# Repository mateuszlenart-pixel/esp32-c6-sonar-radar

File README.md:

# Radar sonarowy ESP32-C6

Firmware dla płytki ESP32-C6-DevKitC-1. Radar obraca serwo, wykonuje pomiary odległości sonarem i pokazuje stan na ekranie OLED oraz matrycy LED. Buzzer sygnalizuje stan krytyczny. Opcjonalna obsługa Wi-Fi działa w trybie stacji.

## Wymagania

- Linux z PlatformIO Core
- ESP32-C6-DevKitC-1 do późniejszego testu sprzętowego
- Płytka nie jest potrzebna do kompilacji ani testów hostowych

## Kompilacja firmware'u

W katalogu repozytorium uruchom:

```bash
$HOME/.platformio/penv/bin/pio run
```

PlatformIO używa środowiska `esp32-c6-devkitc-1` z `platformio.ini`. Kompilacja tworzy pliki w katalogu `.pio/`.

## Testy hostowe

Testy nie wymagają ESP32 ani podłączonych czujników. Uruchom je w katalogu repozytorium:

```bash
gcc -std=c11 -Wall -Wextra -Werror -Isrc src/detector.c tests/test_detector.c -o /tmp/test_detector && /tmp/test_detector
```

```bash
gcc -std=c11 -Wall -Wextra -Werror -Isrc src/scan_control.c tests/test_scan_control.c -o /tmp/test_scan_control && /tmp/test_scan_control
```

```bash
gcc -std=c11 -Wall -Wextra -Werror -Isrc src/usb_cc.c tests/test_usb_cc.c -o /tmp/test_usb_cc && /tmp/test_usb_cc
```

GitHub Actions uruchamia wszystkie trzy zestawy testów oraz kompiluje firmware przy pushu na `main` i przy pull requestach.

## Buzzer

Płytka ma tranzystorowy stopień (Q2) i diodę (D2), więc pasuje zarówno buzzer pasywny, jak i aktywny
na 5 V. W `src/app_config.h` ustaw `BUZZER_ACTIVE`:

- `0` (domyślnie): buzzer pasywny, firmware generuje ton PWM i alarm krytyczny ma wyraźnie inne tony;
- `1`: buzzer aktywny, firmware tylko włącza i wyłącza, a różnice zostają w rytmie sygnału.

## Wi-Fi

Bez lokalnego pliku z danymi Wi-Fi firmware pomija uruchomienie Wi-Fi, a lokalne funkcje radaru nadal działają.

Aby skonfigurować Wi-Fi na swoim komputerze:

1. Skopiuj `src/wifi_credentials.example.h` do `src/wifi_credentials.h`.
2. Wypełnij lokalnie nazwę sieci 2,4 GHz i jej hasło.
3. Skompiluj firmware ponownie.

Plik `src/wifi_credentials.h` jest ignorowany przez Git. Nie umieszczaj danych sieciowych w repozytorium, logach ani wiadomościach.

## Jak działa firmware

- `radar.c` steruje ruchem patrolowym serwa. Patrol obejmuje kąty od 15° do 165° i zatrzymuje się podczas blokady na wykrytym celu.
- `sonar.c` wykonuje pojedynczy pomiar, a `sonar_task.c` przekazuje wyniki dalej.
- `detector.c` wykrywa cel i alarm krytyczny na podstawie kolejnych pomiarów.
- `ui_task.c`, `oled.c`, `matrix.c` i `buzzer.c` obsługują ekran, matrycę i sygnał dźwiękowy.
- `power_monitor.c` mierzy przez ADC napięcie szyny 5 V (GPIO0) oraz linie CC1/CC2 gniazda USB-C zasilania
  (GPIO1, GPIO3) i czyta flagę przeciążenia przełącznika U2 (GPIO23). Co 30 s oraz przy każdej zmianie
  zapisuje wynik w logu i ostrzega, gdy zasilacz podaje tylko 500/900 mA, szyna 5 V spadnie poniżej 4,5 V
  albo U2 ogranicza prąd. Klasyfikacja CC jest w `usb_cc.c` (testy hostowe). Działa na płytce PCB;
  na breadboardzie bez tych elementów odczyty są przypadkowe, a log tylko informacyjny.
- `network.c` obsługuje połączenie Wi-Fi oraz ponawianie połączenia.
- `zigbee_bridge.c` udostępnia czujniki i przełączniki przez Zigbee.
- `mqtt_bridge.c` publikuje stan radaru oraz każdy kolejny pomiar po MQTT.

## Home Assistant, Zigbee2MQTT i MQTT

ESP32-C6 działa jako urządzenie Zigbee typu End Device. Połączenie Wi-Fi i Zigbee
korzysta z tej samej anteny 2,4 GHz, więc End Device ogranicza ryzyko problemów
ze współpracą obu sieci. Koordynator SONOFF Dongle-PMG24 pozostaje podłączony do
Zigbee2MQTT; nie trzeba zmieniać jego firmware.

### Encje Zigbee

Plik `zigbee2mqtt/radar_converter.mjs` opisuje encje dla Zigbee2MQTT. Umieść go
w folderze `external_converters` obok `configuration.yaml` w katalogu danych
Zigbee2MQTT. W dodatku Home Assistanta domyślny katalog danych to
`/config/zigbee2mqtt`, więc pełna ścieżka pliku to
`/config/zigbee2mqtt/external_converters/radar_converter.mjs`.

W Zigbee2MQTT 2.11 lub nowszym włącz `advanced.enable_external_js`. Konwerter
można też dodać lub zmienić w interfejsie Zigbee2MQTT w **Settings → Dev console
→ External converters**. Po dodaniu pliku uruchom ponownie Zigbee2MQTT. Następnie
włącz dozwolone dołączanie urządzeń i uruchom radar. Po wykryciu radaru zaakceptuj
nowe urządzenie.

Zigbee udostępnia wykrycie celu, alarm krytyczny, odległość, kąt, dwa progi
odległości oraz przełączniki patrolu i buzzera. Próg celu można ustawić w zakresie
10–400 cm, a krytyczny w zakresie 5–300 cm. Próg krytyczny musi być mniejszy od
progu celu. Po dołączeniu Z2M konfiguruje raportowanie zmian.

### MQTT i Home Assistant

Skopiuj `src/wifi_credentials.example.h` do lokalnego pliku
`src/wifi_credentials.h`. W tym lokalnym pliku wpisz dane Wi-Fi i adres brokera
MQTT; jeśli broker wymaga logowania, wpisz je tam. Nie wysyłaj tych wartości na
czat i nie dodawaj lokalnego pliku do Git. MQTT Discovery automatycznie tworzy
encje w Home Assistant. Topic `esp32-c6-sonar-radar/<identyfikator>/state`
zawiera aktualny stan, a topic `.../scan` przekazuje kolejne pomiary z kątem,
odległością i informacją, czy pomiar był prawidłowy.

W tej wersji testowano kompilację i logikę programową. Dołączenie urządzenia,
raportowanie Zigbee, encje Home Assistant i fizyczne pomiary wymagają późniejszego
testu z płytką oraz działającym Zigbee2MQTT i brokerem MQTT.

## Test sprzętowy

Szczegółowy plan testów i szkic połączeń znajduje się w
[`docs/hardware/radar-wiring-and-test-plan.md`](docs/hardware/radar-wiring-and-test-plan.md).
Interaktywny model breadboardu (sieci, kontrola zwarć, edycja położenia elementów)
uruchomisz, otwierając w przeglądarce plik
[`docs/hardware/breadboard-model.html`](docs/hardware/breadboard-model.html).

Kompilacja i testy hostowe nie sprawdzają płytki, serwa ani czujników. Przed pierwszym testem sprzętowym należy osobno zweryfikować zasilanie, poziomy napięć i połączenia dla dokładnych modeli modułów. Plik `src/app_config.h` zawiera przypisania GPIO, ale sam w sobie nie jest schematem bezpiecznego okablowania.

### Poziomy napięć do sprawdzenia

- ESP32-C6 pracuje z GPIO w domenie 3,3 V. Jego wejście nie może przekroczyć 3,6 V ([datasheet Espressif, tabele 5-1 i 5-4](https://documentation.espressif.com/esp32-c6_datasheet_en.html)). Nie podłączaj bezpośrednio wyjścia ECHO typowego modułu HC-SR04 zasilanego z 5 V; obniż poziom sygnału przed GPIO. Dokładne wersje HC-SR04 mogą się różnić ([przykładowa dokumentacja modułu Elecfreaks](https://elecfreaks.com/download/EF03085-HC-SR04_Ultrasonic_Module_User_Guide.pdf)).
- Jeśli sam układ MAX7219 jest zasilany napięciem 5 V, jego datasheet wymaga co najmniej 3,5 V na wejściu logicznym. ESP32-C6 gwarantuje dla wyjścia logicznego wysokiego co najmniej 0,8 × 3,3 V = 2,64 V, więc bezpośrednia współpraca nie jest gwarantowana. Trzeba sprawdzić, czy konkretny moduł ma właściwy translator poziomów ([datasheet Analog Devices MAX7219, tabela na stronie 2](https://www.analog.com/media/en/technical-documentation/data-sheets/max7219-max7221.pdf)).

Te uwagi nie zastępują sprawdzenia oznaczeń i schematów dokładnych modułów. Nie podłączaj serwa do zasilania, dopóki jego napięcie i wydajność prądowa nie zostaną potwierdzone dla użytej płytki zasilającej.

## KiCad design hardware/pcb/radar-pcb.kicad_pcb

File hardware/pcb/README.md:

# Płytka PCB radaru (KiCad 10)

> **Stan 2026-10-15: wersja przewlekana v0.2** (76 × 137,5 mm, wszystko lutowane ręcznie, gniazdo DC zamiast USB-C,
> piny DevKita wyprowadzone na listwy, pole prototypowe). Opisy poniżej (USB-C, U2, SMD, rozmieszczenie ręczne)
> dotyczą wcześniejszej wersji SMD v0.1 i są **historyczne**; aktualne decyzje: [`order-notes.md`](order-notes.md).
> Generatory: `tools/gen_schematic.py` (schemat), `tools/autoplace.py` (rozmieszczenie, `tools/geom.py` = kotwice i strefy),
> `tools/gen_pcb.py` (płytka), `tools/build_all.sh` (całość, `SKIP_PLACE=1` używa zapisanego `tools/layout.json`).

Status: **start projektu 2026-10-10.** Zamówienie dopiero po sprawdzeniu na breadboardzie
wszystkich bloków i po kontrakcie mechanicznym (zob. `../README.md`).

## Narzędzia (Dell, Flatpak `org.kicad.KiCad` 10.0.7)

- Biblioteki symboli i footprintów: `/app/extensions/Library/{symbols,footprints,3dmodels}`
  wewnątrz Flatpaka (`flatpak run --command=sh org.kicad.KiCad -c '...'`).
- Python z modułem `pcbnew` (10.0.7) w tym samym Flatpaku: skrypty tworzą i sprawdzają płytkę.
- `kicad-cli`: ERC, DRC, eksport Gerberów, BOM, podgląd 3D.
- Brak Javy, więc bez Freerouting; trasowanie ręczne/skryptem (płytka jest prosta).

## Bloki obwodu (z breadboardu, stan na 2026-10-10)

| Blok | Stan na breadboardzie |
|---|---|
| Zasilanie 5 V z EB2005 | zmierzone (5,13 V) |
| HC-SR04: TRIG przez SN74AHCT125, ECHO przez dzielnik 10 kΩ/15 kΩ | działa, ±1 cm |
| OLED SH1106, I2C, 3,3 V z ESP32 | działa |
| MAX7219 przez kanały 2–4 AHCT125 | zaparkowane, plan gotowy |
| Serwo SG90, 5 V | nie podłączone |
| Buzzer (tranzystor) | nie podłączone, typ nieustalony |

## Domyślne założenia projektowe (DO ZATWIERDZENIA przez użytkownika)

1. **ESP32-C6-DevKitC-1 w gniazdach żeńskich** (decyzja użytkownika z 2026-10-09).
   Rozstaw rzędów do potwierdzenia na posiadanej płytce przed layoutem.
2. **Zasilanie wejściowe (zmiana 2026-10-11):** gniazdo **USB-C tylko do zasilania** (HRO TYPE-C-31-M-12, od 2026-10-14; wcześniej GCT USB4105,
   montaż maszynowy) zamiast gniazda DC. Rezystory 5,1 kΩ na CC1/CC2 (R16, R17) są konieczne, żeby
   ładowarka z kablem USB-C ↔ USB-C podała 5 V. Ochrona: TVS 5 V (D3, SMAJ5.0A, jednokierunkowy) na wejściu oraz przełącznik obciążenia z miękkim startem
   i ogranicznikiem prądu U2 (**AP22802AW5-7**, LCSC C211404, od 2026-10-14; zastąpił AP22804AW5, którego nie ma w katalogu JLCPCB; ten sam układ wyprowadzeń SOT-25, EN aktywny wysokim, EN połączone z VIN, RDS(on) typ. 50 mΩ, limit prądu 2,2–3,2 A, typ. 2,7 A, znamionowo 2 A) zamiast
   bezpiecznika polimerowego (mniejszy spadek napięcia, miękki start i ograniczenie prądu przy ładowaniu ok. 900 µF; patrz uwagi do weryfikacji niżej); zabezpieczenie przed odwrotną polaryzacją (Q1) usunięte, bo USB-C nie da się
   podłączyć odwrotnie. Linie danych USB (D+/D−, SBU) niepodłączone. Wejście 5 V zasila serwo, HC-SR04,
   MAX7219, bufor i ESP32. Wymagana ładowarka ≥ 5 V / 1,5 A (szczyt poboru około 1–1,3 A); port USB
   komputera (500 mA) może nie wystarczyć.
3. **Pin 5V DevKita (J2 pin 14) jest zasilany z +5V płytki przez diodę Schottky D4** (kierunek płytka →
   DevKit). Poprawka po audycie 2026-10-11: DevKit ma własną diodę 1N5819 od swojego USB do pinu 5V,
   więc bezpośrednie połączenie z +5V pozwalałoby, żeby port USB komputera zasilał całą płytkę (serwo,
   matryca, sonar) i zasilał VBUS gniazda USB-C. Z diodą D4 USB DevKita zasila tylko DevKit
   (programowanie), a przy zasilaniu z USB-C płytki DevKit dostaje około 4,7 V przez D4.
4. **Moduły na złączach 2,54 mm** (gniazda żeńskie na PCB): OLED 1×4, MAX7219 1×5,
   HC-SR04 1×4, serwo 1×3. HC-SR04 i serwo na kablach, bo siedzą na obracanej głowicy.
5. **Bufor SN74AHCT125D w SMD (SOIC-14)** (decyzja po audycie 2026-10-11, montaż maszynowy), wszystkie 4
   kanały użyte (TRIG, DIN, CLK, CS), rezystory 47 kΩ na wejściach A: pull-down na TRIG, DIN i CLK,
   **pull-up do 3,3 V na CS** (w firmware CS spoczynkowo wysoki; na płytce testowej działało z pull-downem),
   100 nF przy VCC.
6. **Dzielnik ECHO 10 kΩ/15 kΩ** na płytce, zgodnie z prototypem.
7. **Buzzer:** tranzystor NPN lub MOSFET z rezystorem bazy i diodą (dla cewki), złącze
   2-pinowe na zewnętrzny buzzer. Typ buzzera do identyfikacji.
8. **Kondensatory odsprzęgające i bulk** na szynie 5 V (np. 470 µF przy serwie i MAX7219).
9. **Punkty testowe** na 5 V, 3V3, GND, TRIG, ECHO (węzeł GPIO6).
10. **Wyłącznik ON/standby:** przycisk chwilowy (tact) na GPIO2 do GND (wewnętrzny pull-up ESP32, opcjonalnie kondensator 100 nF do GND), do tego 2-pinowe złącze na zewnętrzny przycisk w obudowie. To „miękki” wyłącznik: ESP32 zostaje włączone (inaczej nie zadziała Zigbee), a serwo, pomiary, ekrany i buzzer są wyłączone. Opcjonalnie dodatkowo twardy przełącznik w linii 5 V (do decyzji).
11. **Obrys i otwory montażowe:** dopiero z kontraktu mechanicznego (kolumna obudowy
    70 × 50 mm, wnętrze mniejsze o ścianki).

## Stan prac (2026-10-10)

- **Schemat:** `radar-pcb.kicad_sch` (A3), generowany skryptem `tools/gen_schematic.py`
  (połączenia przez etykiety globalne, każdy pin ma sieć albo znacznik NC). 36 elementów,
  41 sieci. ERC (`kicad-cli sch erc`): **0 błędów**, 6 ostrzeżeń `lib_symbol_mismatch`
  dla U1 (osadzona kopia 74AHCT125 jest spłaszczona, bez wpływu na połączenia).
- **Pinout DevKita:** `devkit-pinout.md` (odczytany ze schematu Espressif; poprawka: GND jest
  też na J3 pin 12 i 15).
- **Płytka (szkic automatyczny, 2026-10-10):** `radar-pcb.kicad_pcb`, 66 × 128 mm, dwie warstwy,
  generowana skryptem `tools/gen_pcb.py` z netlisty schematu. Układ (widok od frontu): u góry
  złącza kabli do głowicy (sonar, serwo, buzzer, przycisk zewnętrzny), pod nimi gniazda OLED i
  MAX7219 (moduły wtykane od frontu), od tyłu poziomo DevKit (USB po lewej), gniazdo USB-C zasilania i przycisk
  ON/STANDBY na lewej krawędzi między rzędami pinów DevKita, bufor AHCT (SOIC) między rzędami DevKita. Trasowanie: Freerouting 2.5.0
  (jar + Temurin JRE 25, pobrane do `~/tools`, sumy kontrolne zweryfikowane), potem wylewki GND.
- **Stan DRC (2026-10-11, po audycie):** `kicad-cli pcb drc --schematic-parity`: **0 naruszeń
  (także silkscreen), 0 niepołączonych, 0 niezgodności ze schematem**. Freerouting: 0 nietrasowanych.
  Rozmieszczenie jest wrażliwe: przesunięcie części przy rzędach DevKita potrafi zepsuć trasowanie
  (ścieżki przechodzą między pinami rzędu J3), więc po każdej zmianie uruchamiać `build_all.sh`.
  Wszystkie elementy mają ręcznie zaplanowane pozycje (`FIXED` w `gen_pcb.py`), pas 0,9 mm przy
  krawędzi jest wolny od ścieżek, wylewki GND na obu warstwach.
- **Opisy na płytce (silkscreen):** przy każdym złączu nazwa modułu i nazwa każdego pinu (sonar,
  serwo, buzzer, przycisk, OLED, MAX7219), od tyłu opis wszystkich 32 pinów DevKita z kierunkiem
  USB-C, przy elementach oznaczenie z wartością (np. „R6 10k”, „C1 470uF 16V”), polaryzacja
  („+” przy elektrolitach, „K” przy katodach diod, „1” przy pinie 1 bufora), opisy punktów
  testowych, gniazda USB-C i przycisku ON/STANDBY. DRC: 0 naruszeń.
- **Przycisk ON/STANDBY:** kątowy (C&K PTS645VL58-2LFS, footprint `SW_Tactile_SPST_Angled_PTS645Vx58-2LFS`)
  na lewej krawędzi; popychacz wystaje ok. 3,3 mm poza płytkę, w osi 65,75 mm od górnej krawędzi
  (otwór w ściance obudowy). Złącze J9 zostaje na ewentualny przycisk panelowy.
- **Rysunek do weryfikacji:** `renders/radar-pcb-v0.1-wymiary-do-weryfikacji.pdf` (A4, strony 1-2
  w skali 1:1: przód i tył z wymiarami W1-W12 oznaczonymi „?”, strona 3: podgląd 3D). Wymiary
  są w skrypcie (`DIMS` w `gen_pcb.py`), legenda na warstwach Dwgs.User (przód) i Cmts.User (tył).
- **Ochrona przed zakłóceniami matrycy (2026-10-11, z testów na breadboardzie):** filtr RC zasilania
  sonaru (R11 10 Ω + C6 100 µF + C7 100 nF, sieć SR04_VCC na J4 pin 1), rezystory szeregowe
  100 Ω na DIN/CLK/CS do MAX7219 (R12–R14, sieci *_J na J6) i kondensatory przy module (C8 100 µF,
  C9 100 nF). Na breadboardzie przełączanie wierszy MAX7219 i transmisja do niej dawały fałszywe
  echa HC-SR04; firmware obchodzi to gaszeniem matrycy na czas pomiaru (widoczne lekkie mruganie).
  Te elementy mają pozwolić z tego obejścia zrezygnować; nie są jeszcze sprawdzone na płytce.
- **Serwo i buzzer (2026-10-11, analiza zakłóceń przed testem):** serwo SG90 pobiera impulsy prądu
  rzędu setek mA i jest zasilane z tej samej szyny 5 V co sonar, bufor i matryca. Dlatego +5V serwa
  idzie przez FB1 (miejsce na ferryt ≥ 1 A albo zworkę 0 Ω) do sieci SERVO_5V, z C4 220 µF i C10 100 nF
  przy złączu J5 (C4 przeniesiony z lewego pasa pod J5). R15 10 kΩ ciągnie sygnał serwa do masy,
  gdy GPIO10 jest nieustawione (reset, start). Buzzer: C11 100 nF na +5V przy sterowniku Q2/J8
  (przełączanie 2 kHz), dioda D2 już była; C12 100 nF równolegle do buzzera jest miejscem
  opcjonalnym. Nie sprawdzone na sprzęcie.
- **Zmiany po audycie (2026-10-11), wszystkie wdrożone:** D4 (punkt 3 wyżej); pod anteną DevKita
  (x ≥ 57, y 91–121) strefa bez miedzi na obu warstwach, punkty TP1/TP3 przeniesione; TVS jednokierunkowy;
  przełącznik obciążenia U2 zamiast F1 (spadek napięcia, miękki start; pełne odcięcie w STANDBY nie jest
  zrobione, bo ESP32 zasila się z tej samej szyny); FB1 domyślnie zworka 0 Ω; punkt testowy SERVO_5V
  (TP6); przycisk zewnętrzny: R18 1 kΩ szeregowo i R19 10 kΩ pull-up po stronie kabla (J9); pomiar
  napięcia 5 V dla firmware (R20/R21 → IO0, C13); złącze awaryjne J10 (RST, GND, BOOT = IO9: zwarcie
  sąsiednich pinów); miejsca R24/R25 4,7 kΩ na pull-upy I2C (nie montować); CS z pull-upem; bufor SOIC.
  Firmware jeszcze nie czyta ADC. Ścieżka VIN ma 0,5 mm (szersza nie mieści się przy padach USB-C 0,5 mm).
  Pomiary CC1 i CC2 przez ADC (R22/R23 100 kΩ, C14/C15 100 nF → IO1 i IO3) są wdrożone; elementy stoją
  tuż przy pinach 8 i 13 DevKita między rzędami (wcześniejsze ustawienie przy złączu USB-C nie dawało
  się poprowadzić).
- **Układ lewej krawędzi (2026-10-13, decyzja użytkownika):** oba gniazda USB-C (zasilania na froncie, programowania
  DevKita od tyłu) są po lewej stronie; gniazdo zasilania ma oś 100 mm od górnej krawędzi (W6), przycisk
  ON/STANDBY 113 mm (W7), oba między rzędami pinów DevKita (94–117 mm), czyli nisko na płytce. Na prawej
  krawędzi, w strefie anteny DevKita, nie ma już metalu ani miedzi. Przeniesiono za gniazdem: R16/R17 (CC),
  D3 (TVS), U2, C16, LED zasilania (D1/R1, wyżej po lewej), R18/R19/C5 (przycisk), punkty TP2/TP4 i dzielnik
  R20/R21/C13 (na dole). Na obudowie opisać, które gniazdo jest zasilające, a które do programowania.
  **W6 (100 mm), W7 (113 mm), W8 (59 mm) i W9 (92 mm) zatwierdzone przez użytkownika 2026-10-13**; wszystkie wymiary
  W1–W12 w PDF mają teraz „OK”. DRC i trasowanie przechodzą (0 naruszeń).
  Generator usuwa ślepe przelotki po imporcie wyniku Freeroutingu (Freerouting zgłasza 3 nietrasowane
  połączenia, a KiCad po imporcie ma 0 niepołączonych; sprawdzone przez DRC).
- **DevKit (zmierzone 2026-10-13):** laminat 52,0 × 25,4 mm, z anteną 58,5 × 25,4 mm; od pinu 1 do końca
  płytki od strony anteny oraz od pinu 16 do końca od strony USB po ok. 7 mm (zgadza się z (52,0 − 38,1)/2 ≈ 6,95).
  Przy pinie 1 na x = 55 mm laminat sięga x ≈ 62, a antena modułu ok. 68,5 mm, czyli ok. 2,5 mm poza prawą
  krawędź płytki. Strefa bez miedzi (x ≥ 57, y 91–121) obejmuje antenę z zapasem, więc **nie zmienia się**.
  Koniec USB DevKita leży przy x ≈ 10 mm, ok. 10 mm od lewej krawędzi płytki.
- **Moduły (zmierzone 2026-10-13):** OLED SH1106 33,5 × 35,5 mm, piny 13,5 mm od krawędzi do osi pierwszego i
  ostatniego, kolejność VCC, GND, SCK, SDA od strony wyświetlacza; MAX7219 32 × 39 mm, piny 11 mm od krawędzi,
  piny wystają poza obrys na wymiarze 39 mm po ok. 6 mm na stronę; HC-SR04 VCC/TRIG/ECHO/GND i serwo SG90
  3-pin 2,54 mm potwierdzone. Gniazda J7 (OLED) i J6 (MAX7219) są wyśrodkowane na x = 33 mm, co zgadza się z pomiarami.
- **Drugi audyt (2026-10-11), wdrożone:** U2 i C16 stoją tuż przy gnieździe USB-C (VIN jest krótki,
  dalej idzie `+5V` ścieżką 0,6–0,8 mm; wcześniej VIN miał ok. 41 mm i spadek napięcia nie malał); LED
  zasilania (D1, R1) przeniesiona niżej; złącze J10 stoi między rzędami DevKita blisko pinów RST (J1 pin 2)
  i GPIO9 (J3 pin 11), więc linie EN i BOOT są krótkie (wcześniej 63 i 21 mm); FLG z U2 prowadzi do GPIO23
  (J3 pin 5, pull-up R26 10 kΩ do 3,3 V; niski = przeciążenie), firmware do dopisania.
  **J10:** kolejność BOOT, GND, RST. Wgrywanie awaryjne: zworka na BOOT–GND, odłączyć i podłączyć
  zasilanie, wgrać firmware, zdjąć zworkę i zrobić reset (zworka na GND–RST na chwilę). Jedna zworka
  obejmuje tylko jedną parę pinów naraz.
  **Otwór H4** (62,5; 124) leży ok. 8 mm od anteny; zalecane nylonowe śruby i tuleje (metal przy
  antenie obniża zasięg). Położenie otworów jest częścią kontraktu mechanicznego i nie zostało zmienione.
  **Uwagi dla firmware:** odczyt CC1/CC2 (GPIO1, GPIO3) dopiero po kilku sekundach od podłączenia
  (ładowarki PD wysyłają komunikaty po CC), mediana z kilku próbek, wewnętrzne pull-upy na tych pinach
  wyłączone. GPIO0 i GPIO1 to też piny kwarcu 32 kHz; na schemacie DevKitC-1 v1.4 kwarcu nie ma
  (sprawdzone wyszukiwaniem w tekście schematu), więc nie koliduje.
  **Przepięcie (świadomie bez zmiany):** TVS SMAJ5.0A ogranicza impulsy, ale przy trwałym nadnapięciu
  z wadliwej ładowarki (np. 9 V) spali się, a AP22802 nie ma ochrony nadnapięciowej. Zgodna ładowarka
  przy rezystorach 5,1 kΩ na CC nie poda więcej niż 5 V, więc ryzyko jest szczątkowe. Zamiana na eFuse
  z OVP (rodzina TI TPS2595x) wymaga potwierdzenia dostępności, footprintu i karty katalogowej, a
  symbolu nie ma w bibliotece KiCada. Opcja na kolejną rewizję.
  **Do sprawdzenia przed zamówieniem:** wariant AP22802**A**W5-7 (EN aktywny wysokim; potwierdzone
  w karcie katalogowej Diodes: pin 4 EN, A = aktywny wysokim, B = niskim); dopuszczalna pojemność wyjściowa i
  zachowanie przy przegrzaniu (za U2 jest ok. 900 µF, start trwa kilka ms w limicie prądu 2,2–3,2 A; AP22802 startuje wolniej niż AP22804, rise time typ. 2,1 ms przy 4,7 µF);
  start z pełną pojemnością i ładowarką 1,5 A na prototypie. Limit prądu U2 jest wyższy niż 1,5 A
  ładowarek USB-C: chroni przed zwarciem, ale ładowarka ma własne zabezpieczenie.
- **Rendery i PDF:** `tools/export_docs.sh` (po `build_all.sh`).
- **Do sprawdzenia przed zamówieniem:** gniazdo USB-C HRO TYPE-C-31-M-12 (footprint z biblioteki KiCad; zmienione z GCT USB4105-xx-A 2026-10-14) – potwierdzić
  dostępność u wykonawcy montażu; dopuszczalny odstęp 0,19 mm pól GND od otworów pozycjonujących jest
  z zaleceń producenta (ustawione w `.kicad_pro`); położenie gniazd modułów po pomiarach (rozstaw rzędów DevKita zmierzony: 23,1 mm).
- **Obrys 66 × 128 mm i położenie elementów to propozycja** do zatwierdzenia po zmierzeniu
  modułów i DevKita. **Zmierzone 2026-10-13 (suwmiarka 0,05 mm):** rozstaw rzędów DevKita 23,1 mm (W10;
  wcześniej zakładane 23,3), długość listwy 38,1 mm (W11), pin 1 11,0 mm od prawej krawędzi (W12), odstęp
  gniazd OLED–MAX7219 42,0 mm (W5). Otwory M3: H1–H4 tworzą prostokąt 59 × 92 mm, x = 3,5 i 62,5, y = 32 i 124.
- **Odtworzenie całości jednym poleceniem** (z katalogu repo): `hardware/pcb/tools/build_all.sh`
  (schemat, ERC, netlista, rozmieszczenie, Freerouting, wylewki GND, DRC; ok. 1,5 min).
- **Następne:** poprawić rozmieszczenie i trasowanie do DRC bez błędów, przegląd użytkownika w
  KiCadzie, kontrakt mechaniczny.

## Plan pracy

1. Zatwierdzenie założeń powyżej.
2. Kontrakt mechaniczny: ułożenie płytki w kolumnie 70 × 50 × 155 mm.
3. Schemat KiCad (skrypt generujący `.kicad_sch`, ERC bez błędów).
4. Netlista i płytka (`pcbnew` w Pythonie), rozmieszczenie, trasowanie, DRC.
5. Przegląd użytkownika w KiCadzie (podgląd 3D), poprawki.
6. Gerbery, BOM, CPL do JLCPCB lub PCBWay, zamówienie po teście prototypu.

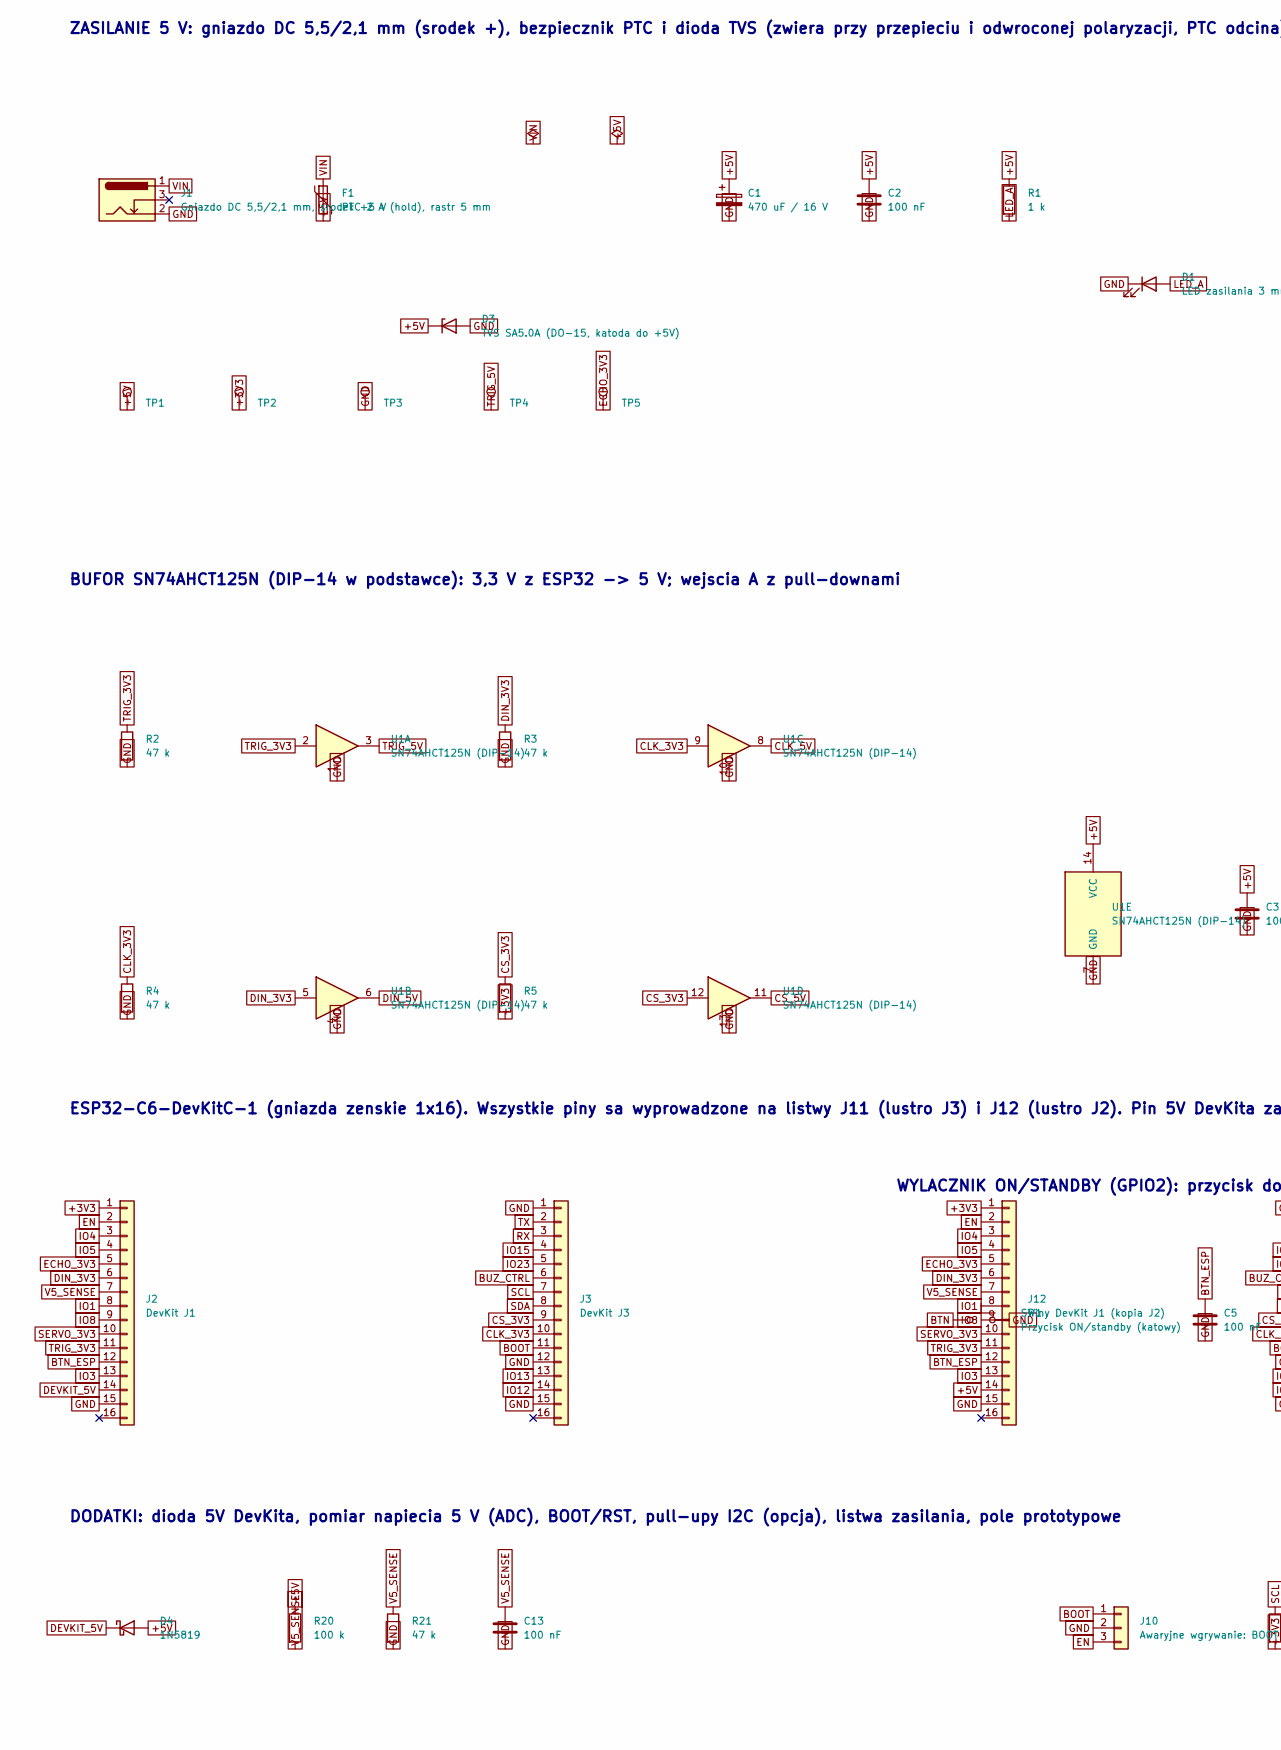
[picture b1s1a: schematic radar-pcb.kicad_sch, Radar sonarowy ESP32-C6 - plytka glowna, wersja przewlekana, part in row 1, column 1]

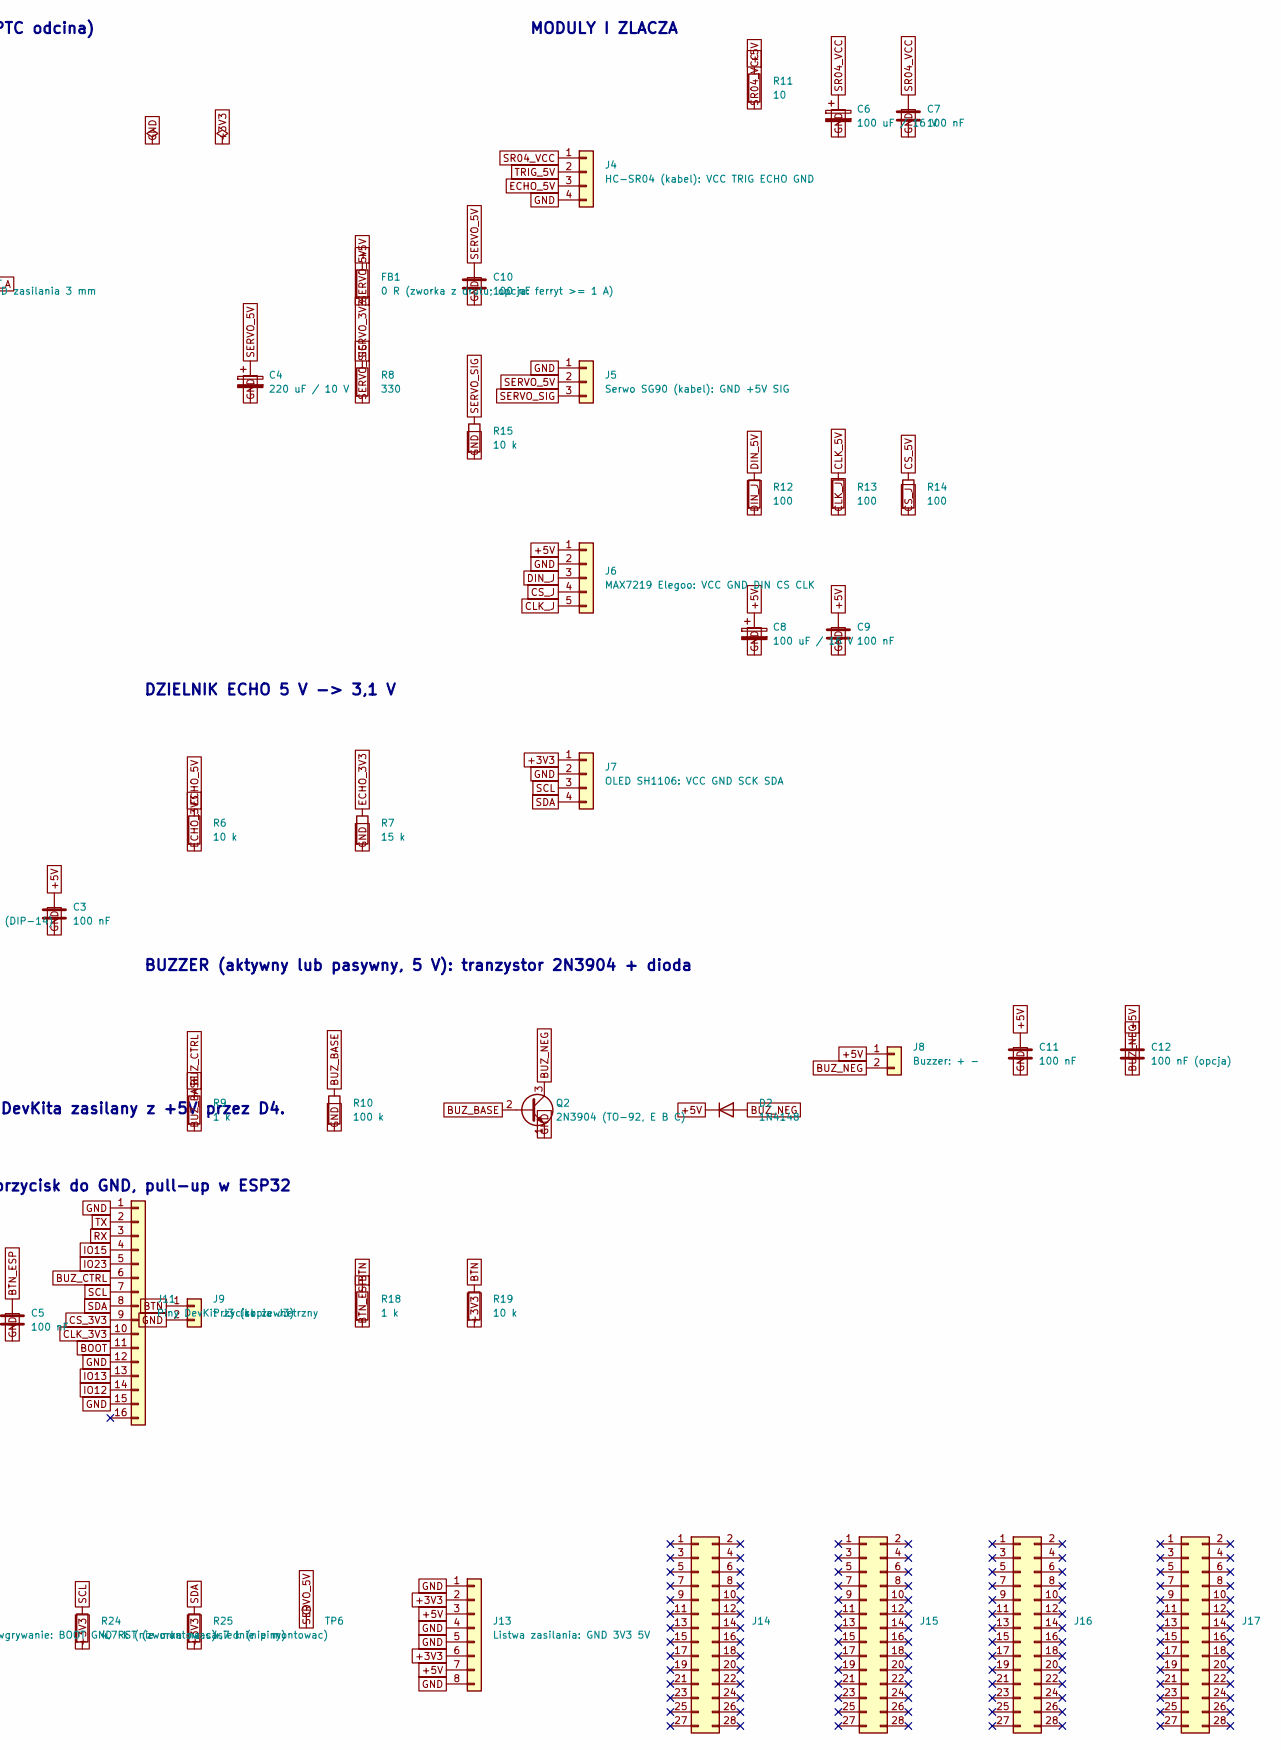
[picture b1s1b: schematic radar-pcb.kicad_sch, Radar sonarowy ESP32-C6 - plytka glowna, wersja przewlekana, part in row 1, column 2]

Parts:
C1: 470 uF / 16 V; CP_Radial_D8.0mm_P3.50mm
C2, C3, C5, C7, C9, C10, C11, C13: 100 nF; C_Disc_D5.0mm_W2.5mm_P5.00mm
C4: 220 uF / 10 V; CP_Radial_D6.3mm_P2.50mm
C6, C8: 100 uF / 16 V; CP_Radial_D6.3mm_P2.50mm
C12: 100 nF (opcja); C_Disc_D5.0mm_W2.5mm_P5.00mm
D1: LED zasilania 3 mm; LED_D3.0mm
D2: 1N4148; D_DO-35_SOD27_P7.62mm_Horizontal
D3: TVS SA5.0A (DO-15, katoda do +5V); D_DO-15_P10.16mm_Horizontal
D4: 1N5819; D_DO-41_SOD81_P10.16mm_Horizontal
F1: PTC 2 A (hold), rastr 5 mm; C_Disc_D7.5mm_W5.0mm_P5.00mm
FB1: 0 R (zworka z drutu; opcja: ferryt >= 1 A); R_Axial_DIN0207_L6.3mm_D2.5mm_P7.62mm_Horizontal
J1: Gniazdo DC 5,5/2,1 mm, srodek +5 V; BarrelJack_Horizontal
J2: DevKit J1; PinSocket_1x16_P2.54mm_Vertical
J3: DevKit J3; PinSocket_1x16_P2.54mm_Vertical
J4: HC-SR04 (kabel): VCC TRIG ECHO GND; PinSocket_1x04_P2.54mm_Vertical
J5: Serwo SG90 (kabel): GND +5V SIG; PinSocket_1x03_P2.54mm_Vertical
J6: MAX7219 Elegoo: VCC GND DIN CS CLK; PinSocket_1x05_P2.54mm_Vertical
J7: OLED SH1106: VCC GND SCK SDA; PinSocket_1x04_P2.54mm_Vertical
J8: Buzzer: + -; PinSocket_1x02_P2.54mm_Vertical
J9: Przycisk zewnetrzny; PinSocket_1x02_P2.54mm_Vertical
J10: Awaryjne wgrywanie: BOOT GND RST (zworka na sasie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; PinSocket_1x03_P2.54mm_Vertical
J11: Piny DevKit J3 (kopia J3); PinSocket_1x16_P2.54mm_Vertical
J12: Piny DevKit J1 (kopia J2); PinSocket_1x16_P2.54mm_Vertical
J13: Listwa zasilania: GND 3V3 5V; PinSocket_1x08_P2.54mm_Vertical
J14: Pole prototypowe 1 (2x14, niepodlaczone); PinHeader_2x14_P2.54mm_Vertical
J15: Pole prototypowe 2 (2x14, niepodlaczone); PinHeader_2x14_P2.54mm_Vertical
J16: Pole prototypowe 3 (2x14, niepodlaczone); PinHeader_2x14_P2.54mm_Vertical
J17: Pole prototypowe 4 (2x14, niepodlaczone); PinHeader_2x14_P2.54mm_Vertical
Q2: 2N3904 (TO-92, E B C); TO-92_Inline
R1, R9, R18: 1 k; R_Axial_DIN0207_L6.3mm_D2.5mm_P7.62mm_Horizontal
R2, R3, R4, R5, R21: 47 k; R_Axial_DIN0207_L6.3mm_D2.5mm_P7.62mm_Horizontal
R6, R15, R19: 10 k; R_Axial_DIN0207_L6.3mm_D2.5mm_P7.62mm_Horizontal
R7: 15 k; R_Axial_DIN0207_L6.3mm_D2.5mm_P7.62mm_Horizontal
R8: 330; R_Axial_DIN0207_L6.3mm_D2.5mm_P7.62mm_Horizontal
R10, R20: 100 k; R_Axial_DIN0207_L6.3mm_D2.5mm_P7.62mm_Horizontal
R11: 10; R_Axial_DIN0207_L6.3mm_D2.5mm_P7.62mm_Horizontal
R12, R13, R14: 100; R_Axial_DIN0207_L6.3mm_D2.5mm_P7.62mm_Horizontal
R24, R25: 4,7 k (nie montowac); R_Axial_DIN0207_L6.3mm_D2.5mm_P7.62mm_Horizontal
SW1: Przycisk ON/standby (katowy); SW_Tactile_SPST_Angled_PTS645Vx58-2LFS
TP1: TP +5V; TestPoint_THTPad_D2.0mm_Drill1.0mm
TP2: TP +3V3; TestPoint_THTPad_D2.0mm_Drill1.0mm
TP3: TP GND; TestPoint_THTPad_D2.0mm_Drill1.0mm
TP4: TP TRIG_5V; TestPoint_THTPad_D2.0mm_Drill1.0mm
TP5: TP ECHO_3V3; TestPoint_THTPad_D2.0mm_Drill1.0mm
TP6: TP SERVO_5V; TestPoint_THTPad_D2.0mm_Drill1.0mm
U1: SN74AHCT125N (DIP-14); DIP-14_W7.62mm_Socket

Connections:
+3V3: J2.1, J7.1, J12.1, J13.2, J13.6, R5.2, R19.2, R24.2, R25.2, TP2.1
+5V: C1.1, C2.1, C3.1, C8.1, C9.1, C11.1, C12.1, D2.1 (K), D3.1 (K), D4.2 (A), F1.2, FB1.1, J6.1, J8.1, J12.14, J13.3, J13.7, R1.1, R11.1, R20.1, TP1.1, U1.14 (VCC)
BOOT: J3.11, J10.1, J11.11
BTN: J9.1, R18.1, R19.1, SW1.1
BTN_ESP: C5.1, J2.12, J12.12, R18.2
BUZ_BASE: Q2.2 (B), R9.2, R10.1
BUZ_CTRL: J3.6, J11.6, R9.1
BUZ_NEG: C12.2, D2.2 (A), J8.2, Q2.3 (C)
CLK_3V3: J3.10, J11.10, R4.1, U1.9
CLK_5V: R13.1, U1.8
CLK_J: J6.5, R13.2
CS_3V3: J3.9, J11.9, R5.1, U1.12
CS_5V: R14.1, U1.11
CS_J: J6.4, R14.2
DEVKIT_5V: D4.1 (K), J2.14
DIN_3V3: J2.6, J12.6, R3.1, U1.5
DIN_5V: R12.1, U1.6
DIN_J: J6.3, R12.2
ECHO_3V3: J2.5, J12.5, R6.2, R7.1, TP5.1
ECHO_5V: J4.3, R6.1
EN: J2.2, J10.3, J12.2
GND: C1.2, C2.2, C3.2, C4.2, C5.2, C6.2, C7.2, C8.2, C9.2, C10.2, C11.2, C13.2, D1.1 (K), D3.2 (A), J1.2, J2.15, J3.1, J3.12, J3.15, J4.4, J5.1, J6.2, J7.2, J9.2, J10.2, J11.1, J11.12, J11.15, J12.15, J13.1, J13.4, J13.5, J13.8, Q2.1 (E), R2.2, R3.2, R4.2, R7.2, R10.2, R15.2, R21.2, SW1.2, TP3.1, U1.1, U1.4, U1.7 (GND), U1.10, U1.13
IO1: J2.8, J12.8
IO3: J2.13, J12.13
IO4: J2.3, J12.3
IO5: J2.4, J12.4
IO8: J2.9, J12.9
IO12: J3.14, J11.14
IO13: J3.13, J11.13
IO15: J3.4, J11.4
IO23: J3.5, J11.5
LED_A: D1.2 (A), R1.2
RX: J3.3, J11.3
SCL: J3.7, J7.3, J11.7, R24.1
SDA: J3.8, J7.4, J11.8, R25.1
SERVO_3V3: J2.10, J12.10, R8.1
SERVO_5V: C4.1, C10.1, FB1.2, J5.2, TP6.1
SERVO_SIG: J5.3, R8.2, R15.1
SR04_VCC: C6.1, C7.1, J4.1, R11.2
TRIG_3V3: J2.11, J12.11, R2.1, U1.2
TRIG_5V: J4.2, TP4.1, U1.3
TX: J3.2, J11.2
V5_SENSE: C13.1, J2.7, J12.7, R20.2, R21.1
VIN: F1.1, J1.1

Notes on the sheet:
ZASILANIE 5 V: gniazdo DC 5,5/2,1 mm (srodek +), bezpiecznik PTC i dioda TVS (zwiera przy przepieciu i odwroconej polaryzacji, PTC odcina)
BUFOR SN74AHCT125N (DIP-14 w podstawce): 3,3 V z ESP32 -> 5 V; wejscia A z pull-downami
DZIELNIK ECHO 5 V -> 3,1 V
ESP32-C6-DevKitC-1 (gniazda zenskie 1x16). Wszystkie piny sa wyprowadzone na listwy J11 (lustro J3) i J12 (lustro J2). Pin 5V DevKita zasilany z +5V przez D4.
MODULY I ZLACZA
BUZZER (aktywny lub pasywny, 5 V): tranzystor 2N3904 + dioda
WYLACZNIK ON/STANDBY (GPIO2): przycisk do GND, pull-up w ESP32
DODATKI: dioda 5V DevKita, pomiar napiecia 5 V (ADC), BOOT/RST, pull-upy I2C (opcja), listwa zasilania, pole prototypowe

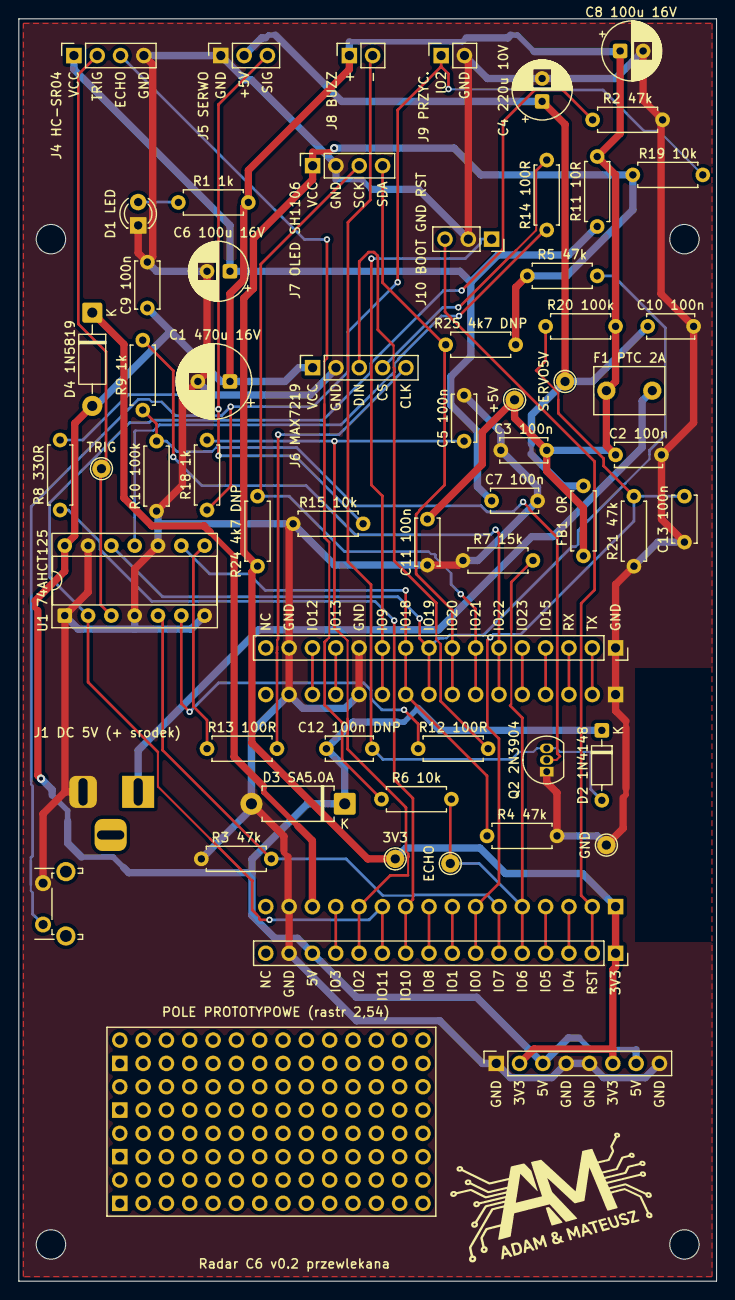
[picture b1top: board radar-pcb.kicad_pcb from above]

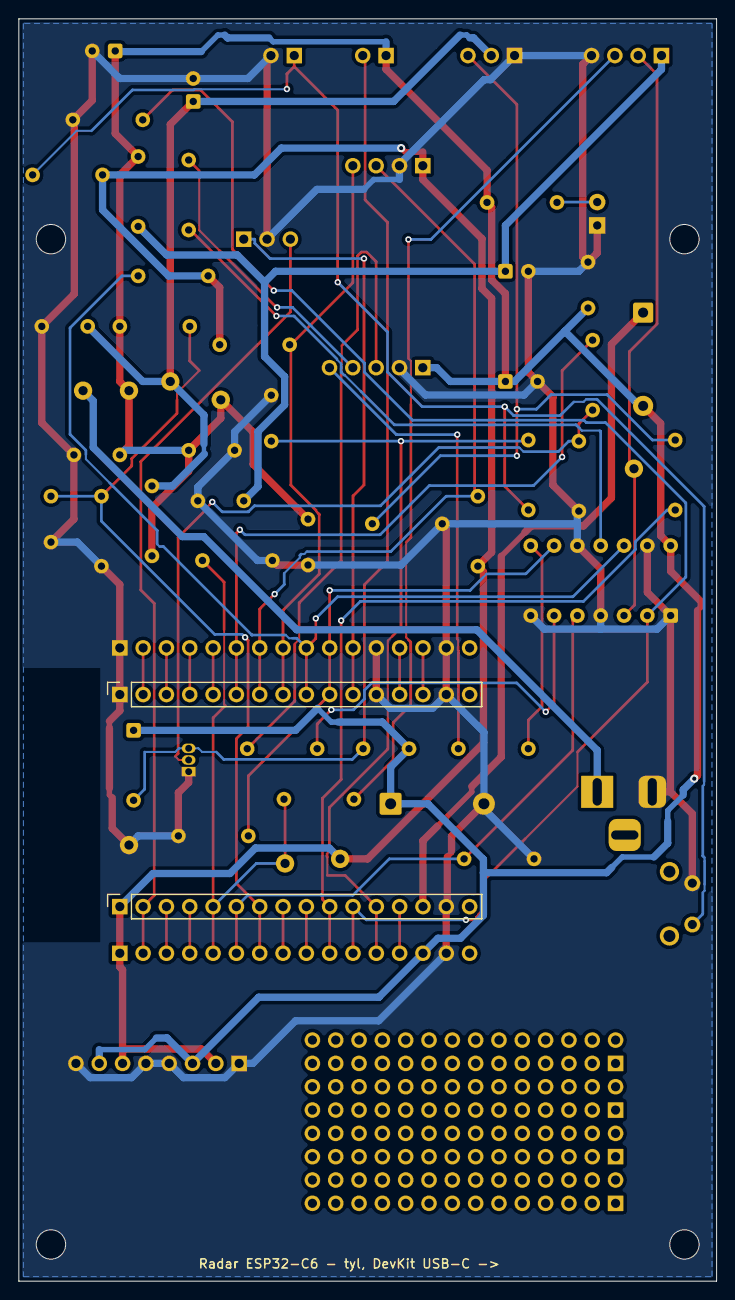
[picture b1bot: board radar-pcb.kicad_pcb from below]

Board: 2 copper layers, 76.0 x 137.5 mm, 71 parts (2 on the bottom side), 44 nets.

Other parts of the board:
H1, H2, H3, H4: MountingHole_3.2mm_M3
LOGO: am-logo
